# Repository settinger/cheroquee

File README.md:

# Cheroquee

A proof-of-concept scrolling LED marquee with support for Cherokee input. Could easily be extended to support variable-width glyphs, fancier scrolling, pre-programmed text cycles, etc. Potentially useful as a starting point for other orthographies that don't have pixel fonts: Inuktitut, N'Ko, maybe vertical Mongolian?

Requires [py-spidev](https://pypi.org/project/spidev/). `pip install py-spidev`

Usage: `python3 cheroquee.py MESSAGE`, e.g. `python3 cheroquee.py "ᏣᎳᎩᎯ ᎠᏰᎵ"`

For more info: www.settinger.net/projects.php?project=cheroquee

* * * * *

## Cultural note

Let's be clear, I'm a white non-Cherokee-speaker showing off a potential tech tool for Cherokee-speakers. I worry about being insensitive, insulting, condescending, or inaccurate; I strive to be none of those things as I present this project. But if I screw up or speak out-of-turn, please tell me!

My scope and intentions are pretty small, here. There's a long history of prescriptivist anglophones unceremoniously thrusting new language tools on people, and I am not trying to be that! There are lots of immediately-apparent ways to improve it, however, **I'll only continue this project if someone else has a real, acceptable use for it**. If you write to me with one, I'll work with you at whatever level of involvement you deem appropriate. Thanks.

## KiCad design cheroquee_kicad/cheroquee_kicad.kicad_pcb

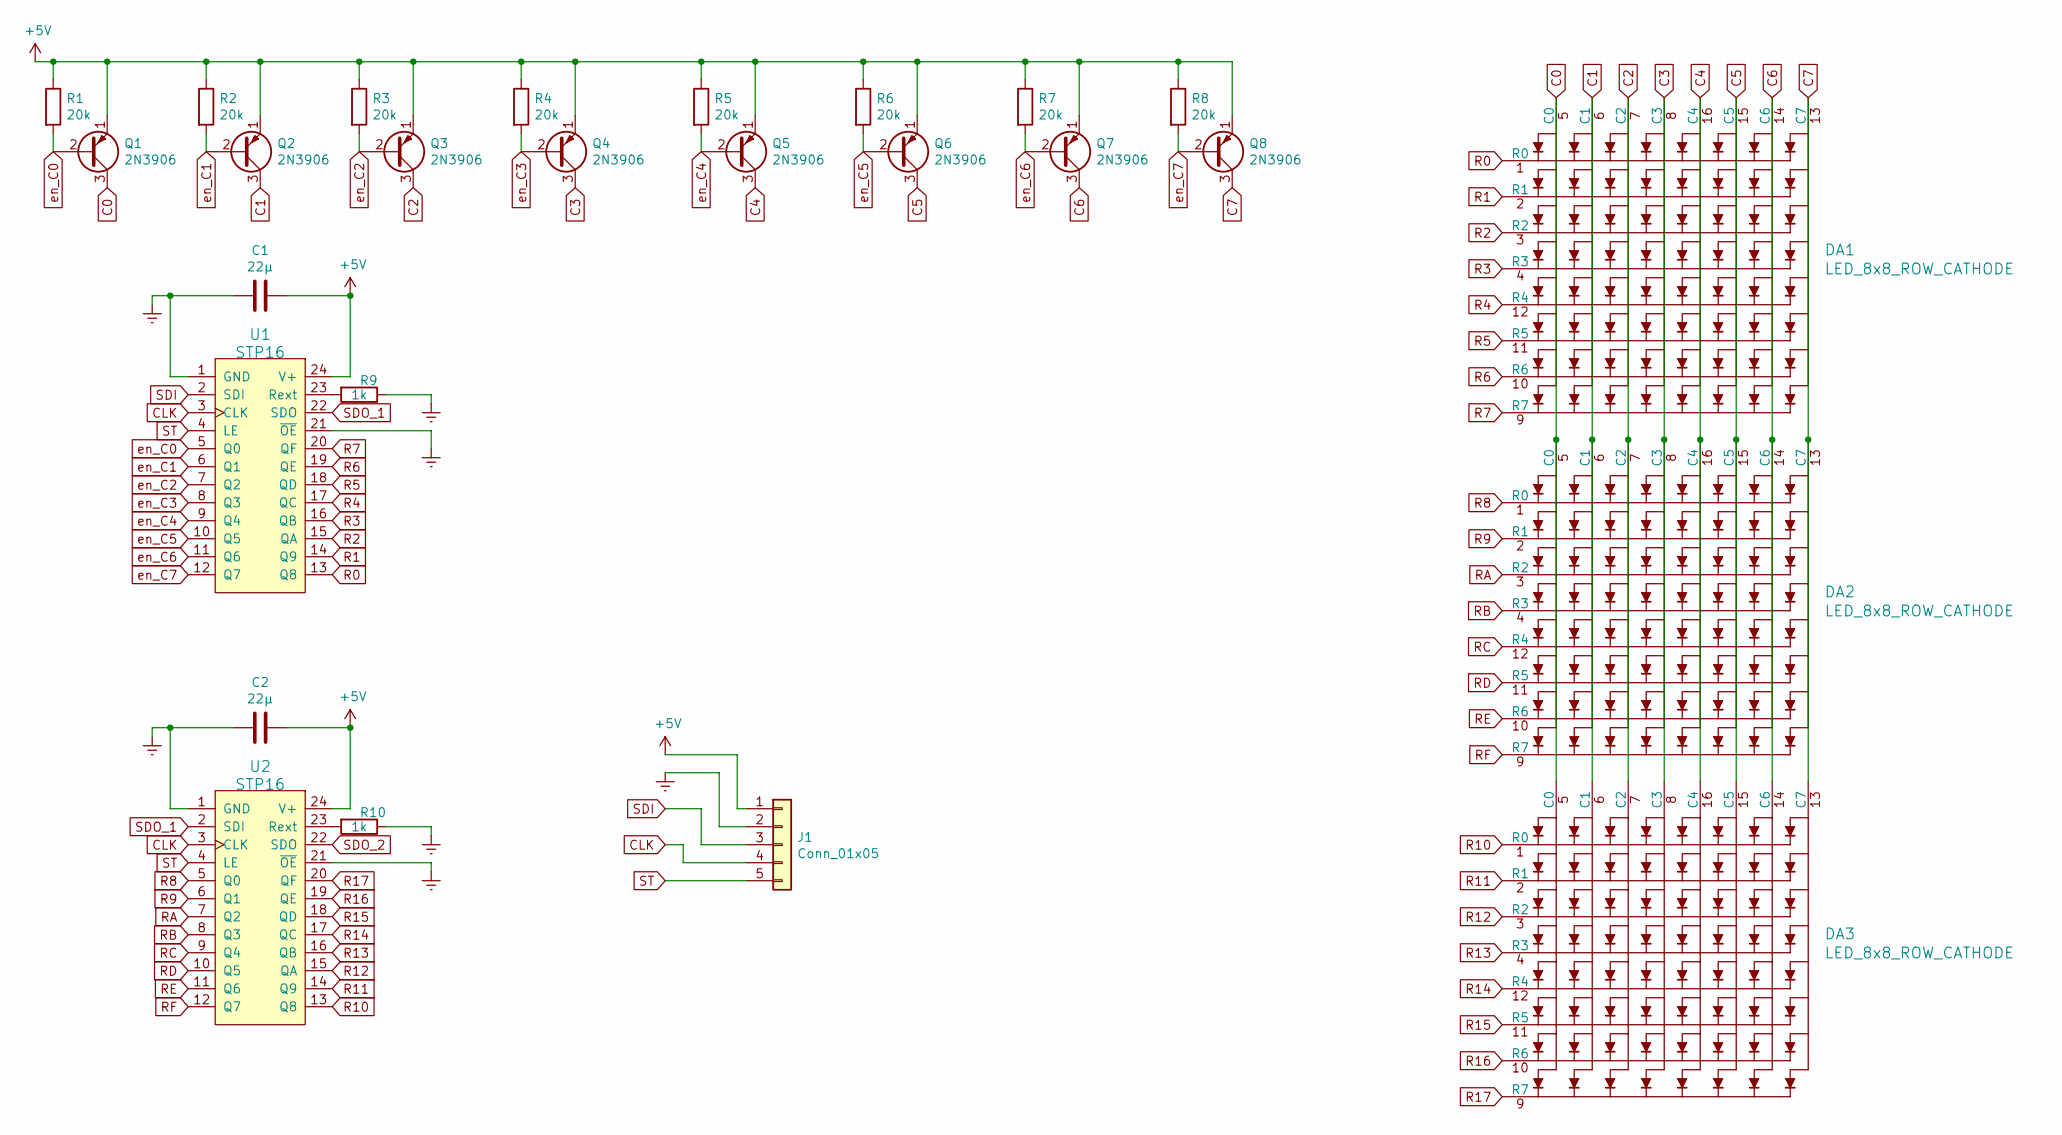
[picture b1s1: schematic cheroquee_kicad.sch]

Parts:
C1, C2: 22μ; Pin_Header_Straight_1x02_Pitch2.54mm
DA1, DA2, DA3: LED_8x8_ROW_CATHODE; 8x8_LED
J1: Conn_01x05; Socket_Strip_Straight_1x05_Pitch2.54mm
Q1, Q2, Q3, Q4, Q5, Q6, Q7, Q8: 2N3906; breadboard_transistor
R1, R2, R3, R4, R5, R6, R7, R8: 20k; Pin_Header_Straight_1x02_Pitch2.54mm
R9, R10: 1k; Pin_Header_Straight_1x02_Pitch2.54mm
U1, U2: STP16; stp16_breakout

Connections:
+5V: C1.1, C2.1, J1.1, Q1.1 (E), Q2.1 (E), Q3.1 (E), Q4.1 (E), Q5.1 (E), Q6.1 (E), Q7.1 (E), Q8.1 (E), R1.1, R2.1, R3.1, R4.1, R5.1, R6.1, R7.1, R8.1, U1.24 (V+), U2.24 (V+)
C0: DA1.5 (C0), DA2.5 (C0), DA3.5 (C0), Q1.3 (C)
C1: DA1.6 (C1), DA2.6 (C1), DA3.6 (C1), Q2.3 (C)
C2: DA1.7 (C2), DA2.7 (C2), DA3.7 (C2), Q3.3 (C)
C3: DA1.8 (C3), DA2.8 (C3), DA3.8 (C3), Q4.3 (C)
C4: DA1.16 (C4), DA2.16 (C4), DA3.16 (C4), Q5.3 (C)
C5: DA1.15 (C5), DA2.15 (C5), DA3.15 (C5), Q6.3 (C)
C6: DA1.14 (C6), DA2.14 (C6), DA3.14 (C6), Q7.3 (C)
C7: DA1.13 (C7), DA2.13 (C7), DA3.13 (C7), Q8.3 (C)
CLK: J1.4, U1.3 (CLK), U2.3 (CLK)
unnamed: R9.2, U1.23 (Rext)
unnamed: R10.2, U2.23 (Rext)
R0: DA1.1 (R0), U1.13 (Q8)
R1: DA1.2 (R1), U1.14 (Q9)
R2: DA1.3 (R2), U1.15 (QA)
R3: DA1.4 (R3), U1.16 (QB)
R4: DA1.12 (R4), U1.17 (QC)
R5: DA1.11 (R5), U1.18 (QD)
R6: DA1.10 (R6), U1.19 (QE)
R7: DA1.9 (R7), U1.20 (QF)
R8: DA2.1 (R0), U2.5 (Q0)
R9: DA2.2 (R1), U2.6 (Q1)
R10: DA3.1 (R0), U2.13 (Q8)
R11: DA3.2 (R1), U2.14 (Q9)
R12: DA3.3 (R2), U2.15 (QA)
R13: DA3.4 (R3), U2.16 (QB)
R14: DA3.12 (R4), U2.17 (QC)
R15: DA3.11 (R5), U2.18 (QD)
R16: DA3.10 (R6), U2.19 (QE)
R17: DA3.9 (R7), U2.20 (QF)
RA: DA2.3 (R2), U2.7 (Q2)
RB: DA2.4 (R3), U2.8 (Q3)
RC: DA2.12 (R4), U2.9 (Q4)
RD: DA2.11 (R5), U2.10 (Q5)
RE: DA2.10 (R6), U2.11 (Q6)
RF: DA2.9 (R7), U2.12 (Q7)
SDI: J1.3, U1.2 (SDI)
SDO_1: U1.22 (SDO), U2.2 (SDI)
SDO_2: U2.22 (SDO)
ST: J1.5, U1.4 (LE), U2.4 (LE)
en_C0: Q1.2 (B), R1.2, U1.5 (Q0)
en_C1: Q2.2 (B), R2.2, U1.6 (Q1)
en_C2: Q3.2 (B), R3.2, U1.7 (Q2)
en_C3: Q4.2 (B), R4.2, U1.8 (Q3)
en_C4: Q5.2 (B), R5.2, U1.9 (Q4)
en_C5: Q6.2 (B), R6.2, U1.10 (Q5)
en_C6: Q7.2 (B), R7.2, U1.11 (Q6)
en_C7: Q8.2 (B), R8.2, U1.12 (Q7)

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
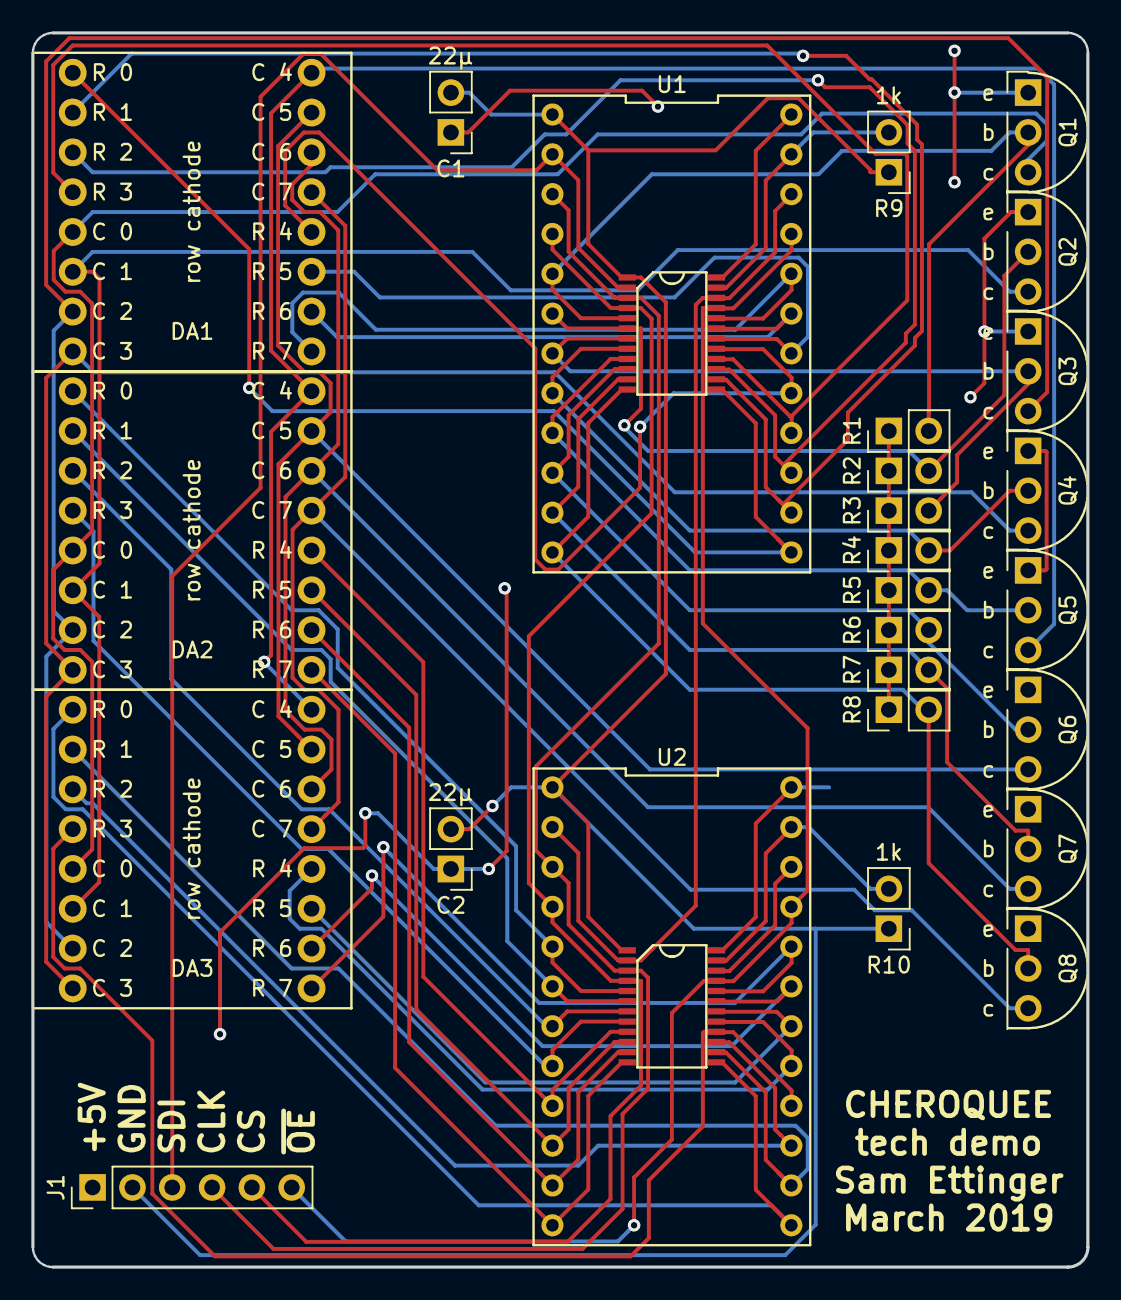
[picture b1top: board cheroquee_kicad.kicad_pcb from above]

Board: 2 copper layers, 67.3 x 78.7 mm, 26 parts (0 on the bottom side), 49 nets.

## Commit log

2019-03-17 Added gitignore
2019-03-17 Rearranged array to match circuit that (should) be arriving soon
2019-03-17 Added the u'' prefix that's apparently required in Python terminal but not in IDLE
2019-03-20 testing SPI as found on github.com/doceme/py-spidev
2019-03-20 system works, but refresh rate is poor
2019-03-20 trying to fix an error
2019-03-23 Update the protoboard
2019-03-23 embracing spidev library over my software serial implementation
2019-03-23 bugfixes
2019-03-23 bugfix
